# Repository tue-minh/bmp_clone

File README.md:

# 🚀 How to Load Firmware into STM32F103C8T6 (Bluepill)

This guide provides detailed instructions for loading Blackmagic firmware onto the Bluepill board using either an ST-Link or Black Magic Probe (BMP).

<table align="center">
  <tr>
    <th>Front</th>
    <th>Back</th>
  </tr>
  <tr>
    <td></td>
    <td></td>
  </tr>
</table>

---

## 📂 1. Prepare the Firmware Files
Locate the following files in your build directory:
- `.../blackmagic-firmware-v1.10.2/bluepill/blackmagic_dfu-bluepill.elf`
- `.../blackmagic-firmware-v1.10.2/bluepill/blackmagic-bluepill.elf`

---

## 🛠️ 2. Install GDB Tool
Open **PowerShell** or **Terminal** and run the following command:
```bash
arm-none-eabi-gdb
```

> **Tip:**
> If GDB is not installed, you can use the version included with PlatformIO by running:
> ```powershell
> # Check the path
> dir $env:USERPROFILE\.platformio\packages\toolchain-gccarmnoneeabi\bin
>
> # Run GDB directly
> & "$env:USERPROFILE\.platformio\packages\toolchain-gccarmnoneeabi\bin\arm-none-eabi-gdb.exe"
> ```

---

## ⚡ 3. Flash the Firmware

Choose your preferred flashing method:

### 🔹 Method A: Using ST-LINK
Use the `st-flash` tool to flash the firmware via the SWD interface:
```bash
# Erase old memory
st-flash erase

# Flash the DFU Bootloader (at address 0x8000000)
st-flash --flash=0x20000 write .../blackmagic-firmware-v1.10.2/bluepill/blackmagic_dfu-bluepill.elf 0x8000000

# Flash the main firmware (at address 0x8002000) and reset
st-flash --flash=0x20000 --reset write .../blackmagic-firmware-v1.10.2/bluepill/blackmagic-bluepill.elf 0x8002000
```

### 🔹 Method B: Using Black Magic Probe (BMP)
Run GDB and execute the following commands:
```bash
# Connect to BMP (replace COMx with the appropriate port)
target extended-remote COMx           # For Windows
target extended-remote /dev/tty*      # For Linux

monitor swdp_scan
attach 1
monitor halt
monitor erase_mass

# Flash the DFU Bootloader
file .../blackmagic-firmware-v1.10.2/bluepill/blackmagic_dfu-bluepill.elf
load

# Flash the main firmware
file .../blackmagic-firmware-v1.10.2/bluepill/blackmagic-bluepill.elf
load

monitor reset
continue
```

---

## 🧠 Important Notes

### Flash Memory Addresses
- The `.elf` files usually contain the address information, so manual specification is often unnecessary.
- STM32F103 Flash starts at `0x08000000`.
  - **DFU Bootloader:** Typically occupies the first 8KB (`0x08000000 → 0x08002000`).

### ✅ Result
After successfully flashing, disconnect and reconnect the board to your PC via USB. If successful, your computer will detect two Virtual COM ports:
1. **GDB Port**
2. **UART Port**

Congratulations! Enjoy your new Blackmagic Probe! 🎉

---

## 📞 Quick Troubleshooting

| **Error**               | **Cause**                  | **Solution**                          |
|-------------------------|----------------------------|---------------------------------------|
| `unknown architecture "arm"` | Incorrect GDB version      | Use the correct `arm-none-eabi-gdb`. |
| `load failed`           | Memory not erased          | Run `monitor erase_mass` before loading. |
| `attach` error          | Physical connection issue  | Check the `monitor swdp_scan` command. |
| Target not detected     | Loose or incorrect SWD wires | Verify SWDIO and SWCLK connections.  |

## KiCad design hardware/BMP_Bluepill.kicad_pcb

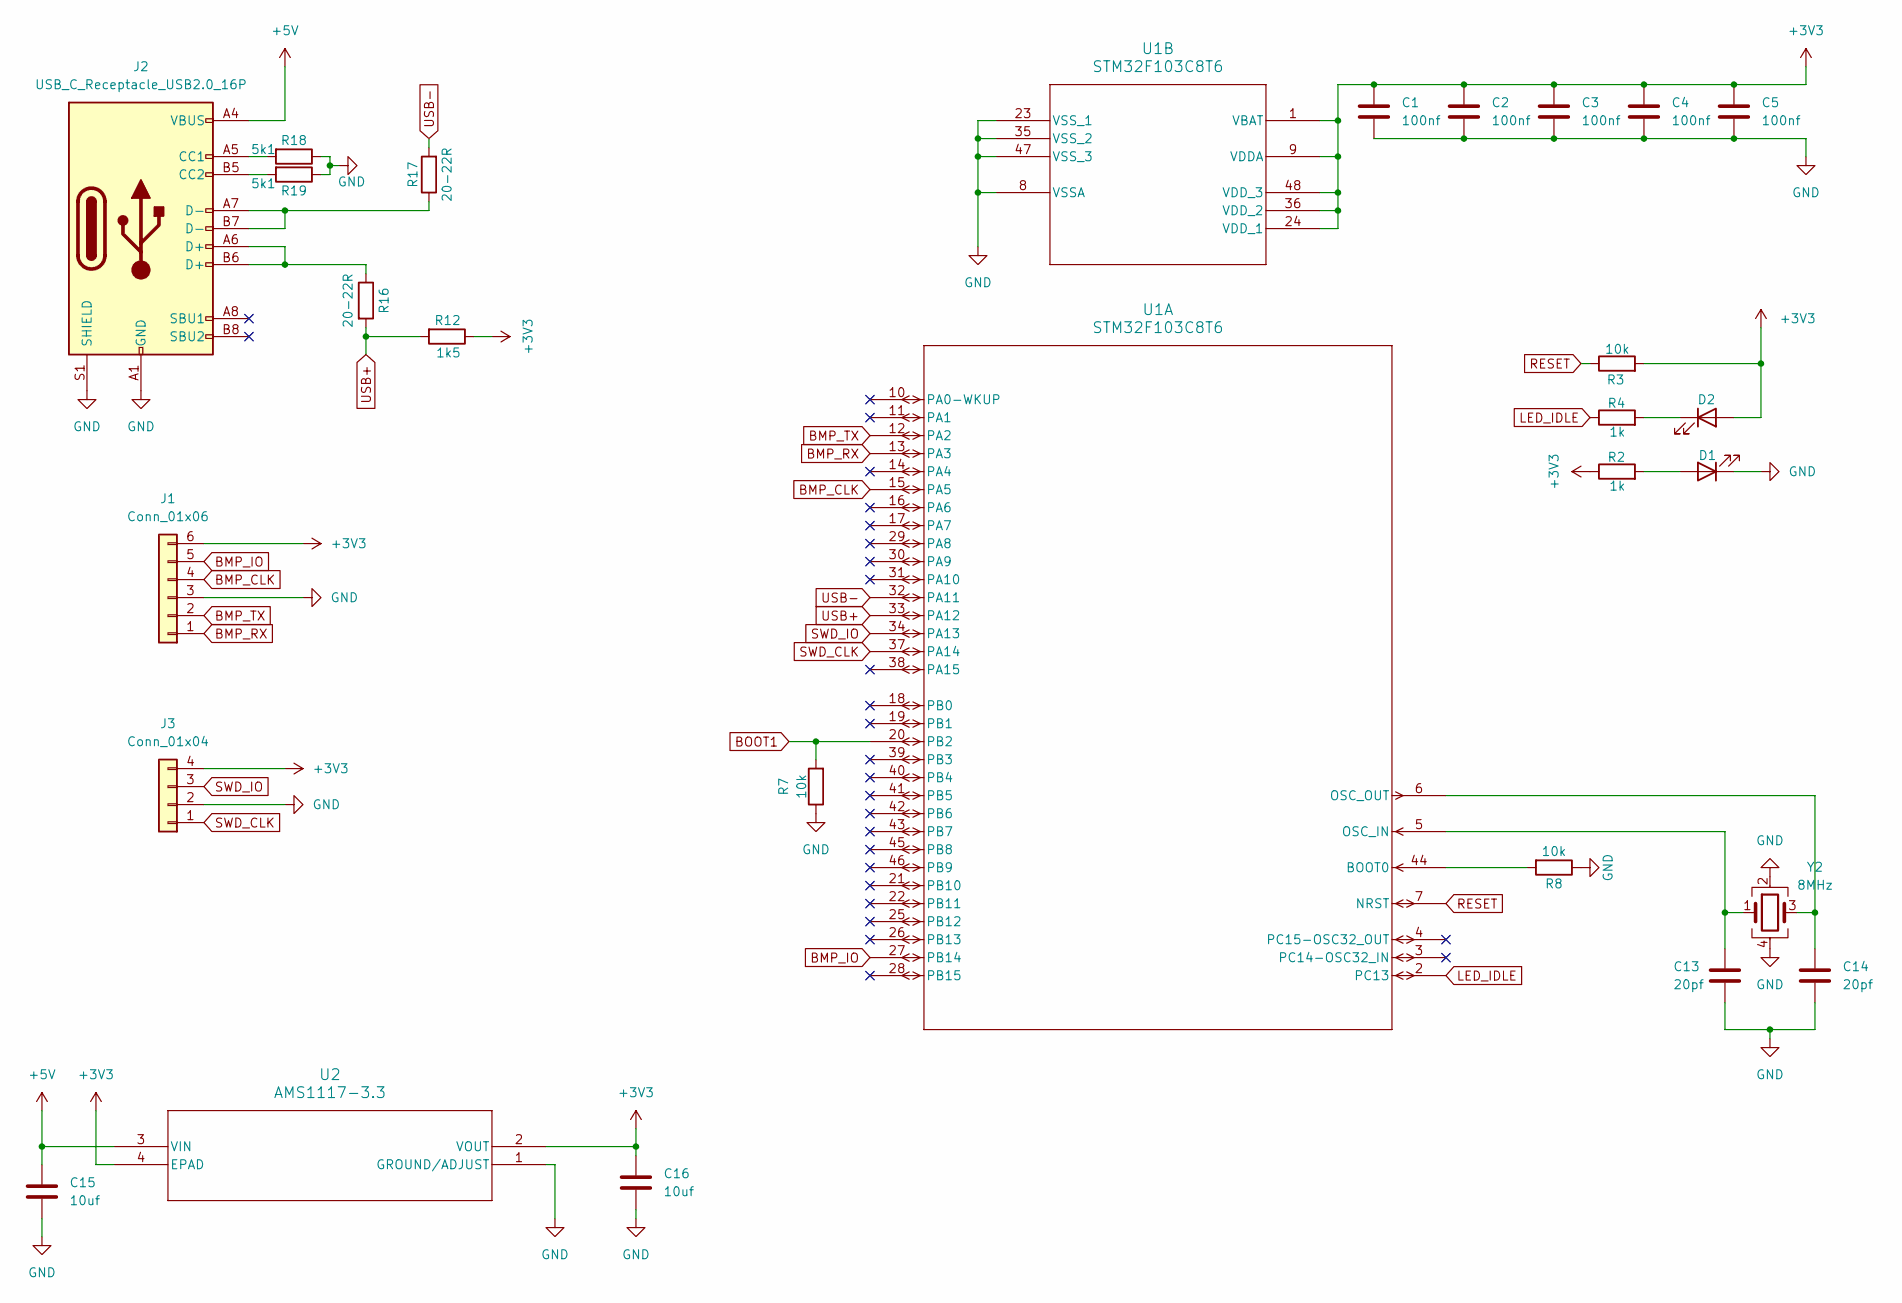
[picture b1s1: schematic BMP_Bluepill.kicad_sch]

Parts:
C1, C2, C3, C4, C5: 100nf; C_0603_1608Metric_Pad1.08x0.95mm_HandSolder
C13, C14: 20pf; C_0603_1608Metric_Pad1.08x0.95mm_HandSolder
C15, C16: 10uf; C_0603_1608Metric_Pad1.08x0.95mm_HandSolder
D1, D2: LED; LED_0603_1608Metric_Pad1.05x0.95mm_HandSolder
J1: Conn_01x06; JST_XH_B6B-XH-A_1x06_P2.50mm_Vertical
J2: USB_C_Receptacle_USB2.0_16P; USB_C_Receptacle_GCT_USB4105-xx-A_16P_TopMnt_Horizontal
J3: Conn_01x04; PinSocket_1x04_P2.54mm_Vertical
R2, R4: 1k; R_0603_1608Metric_Pad0.98x0.95mm_HandSolder
R3, R7, R8: 10k; R_0603_1608Metric_Pad0.98x0.95mm_HandSolder
R12: 1k5; R_0603_1608Metric_Pad0.98x0.95mm_HandSolder
R16, R17: 20-22R; R_0603_1608Metric_Pad0.98x0.95mm_HandSolder
R18, R19: 5k1; R_0603_1608Metric_Pad0.98x0.95mm_HandSolder
U1: STM32F103C8T6; LQFP48_STM
U2: AMS1117-3.3; SOT_AMS_ADS
Y2: 8MHz; Crystal_SMD_5032-4Pin_5.0x3.2mm

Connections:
+3V3: C1.1, C2.1, C3.1, C4.1, C5.1, C16.1, D2.2 (A), J1.6, J3.4, R2.1, R3.2, R12.1, U1.1 (VBAT), U1.9 (VDDA), U1.24 (VDD_1), U1.36 (VDD_2), U1.48 (VDD_3), U2.2 (VOUT), U2.4 (EPAD)
+5V: C15.1, J2.A4 (VBUS), J2.A9 (VBUS), J2.B4 (VBUS), J2.B9 (VBUS), U2.3 (VIN)
BMP_CLK: J1.4, U1.15 (PA5)
BMP_IO: J1.5, U1.27 (PB14)
BMP_RX: J1.1, U1.13 (PA3)
BMP_TX: J1.2, U1.12 (PA2)
BOOT1: R7.2, U1.20 (PB2)
GND: C1.2, C2.2, C3.2, C4.2, C5.2, C13.2, C14.2, C15.2, C16.2, D1.1 (K), J1.3, J2.A1 (GND), J2.A12 (GND), J2.B1 (GND), J2.B12 (GND), J2.S1 (SHIELD), J3.2, R7.1, R8.1, R18.1, R19.1, U1.8 (VSSA), U1.23 (VSS_1), U1.35 (VSS_2), U1.47 (VSS_3), U2.1 (GROUND/ADJUST), Y2.2, Y2.4
LED_IDLE: R4.1, U1.2 (PC13)
unnamed: D1.2 (A), R2.2
unnamed: D2.1 (K), R4.2
unnamed: J2.A5 (CC1), R18.2
unnamed: J2.B5 (CC2), R19.2
unnamed: J2.A6 (D+), J2.B6 (D+), R16.1
unnamed: J2.A7 (D-), J2.B7 (D-), R17.1
unnamed: R8.2, U1.44 (BOOT0)
unnamed: C13.1, U1.5 (OSC_IN), Y2.1
unnamed: C14.1, U1.6 (OSC_OUT), Y2.3
RESET: R3.1, U1.7 (NRST)
SWD_CLK: J3.1, U1.37 (PA14)
SWD_IO: J3.3, U1.34 (PA13)
USB+: R12.2, R16.2, U1.33 (PA12)
USB-: R17.2, U1.32 (PA11)

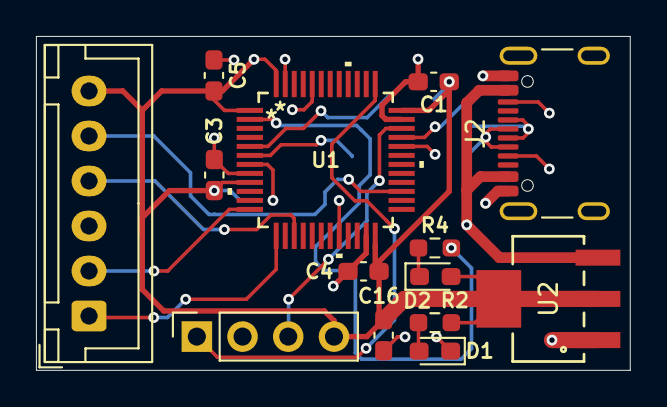
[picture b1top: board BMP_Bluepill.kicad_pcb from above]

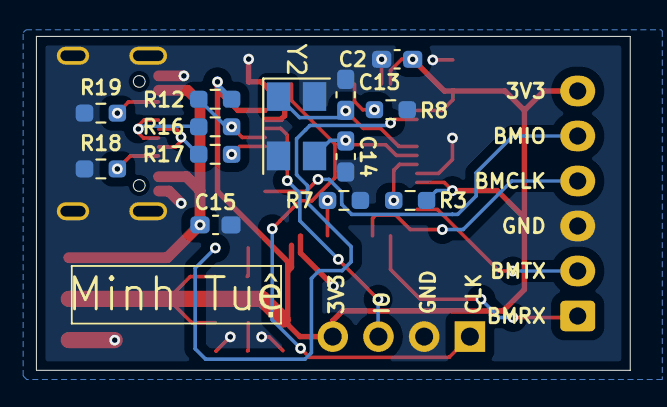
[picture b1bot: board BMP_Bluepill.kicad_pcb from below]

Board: 2 copper layers, 33.0 x 18.5 mm, 27 parts (13 on the bottom side), 23 nets.

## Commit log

2026-03-03 fix layout
2026-03-28 add markdown, add firmware file
2026-03-28 clear trash file
2026-03-29 update README image
2026-03-29 relocate file
2026-05-01 update layout
